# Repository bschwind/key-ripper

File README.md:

# key-ripper

A keyboard personalized for myself, designed in KiCad, with custom firmware written in Rust.

The story behind this board can be found in [this reddit post](https://www.reddit.com/r/MechanicalKeyboards/comments/vtlujd/i_built_a_keyboard_pcb_and_wrote_firmware_for_it/).

I also gave a (time-constrained) talk on making this keyboard which you can view [here](https://www.youtube.com/watch?v=x7LQevYn7d0).
Sadly I didn't get to cover everything I wanted to talk about when it comes to embedded Rust, but I hope you find it entertaining.

## Main Features and Requirements

* Be cheap to manufacture (can easily be ordered and fabricated by JLCPCB, uses an RP2040)
* USB C Connector
* Have dedicated function keys
* Reduce friction changing between a macbook keyboard and this one
* Stay relatively compact
* Full sized arrow keys with a gap (on the left and right) for easily finding the up arrow without looking
* No right shift key (this allows for the arrow keys to sit below the Enter key, and I never use right shift)
* Support for screw-in stabilizers first and foremost, along with snap-in stabilizers, and plate-mounted stabilizers when using a top plate
* Can sit on top of a macbook keyboard
* Easy to assemble - order a PCB, press it into the 3D printed case, and use 4 optional screws if the fit isn't snug
* Firmware written in Rust, debuggable with knurling-rs

## Setup

* Order a PCB with the production files from the [latest release](https://github.com/bschwind/key-ripper/releases).
* When you receive the board, plug it in via USB C and follow [the instruction to flash the firmware](https://github.com/bschwind/key-ripper/blob/main/firmware/README.md).

## 3D Printed Case

The STEP files for the case are available in the [case directory](./case).

They were produced with Rust bindings to OpenCascade. You can find the code for the keyboard case [here](https://github.com/bschwind/opencascade-rs/blob/2eefc2c0322c1cb65bd3279fbedeba416aef8858/examples/src/keyboard_case.rs).

The case can be printed as two separate parts with a dovetail connection (use your slicer and cut up the parts for whatever suits your print bed size), or it can be printed as one full piece.

The PCB can then be slotted into the case with the top edge first (the edge with the USB connector), then press the bottom edge in to fit it into the case. It's usually a snug fit. You can then use 4 M2x4 flat head "laptop screws" to secure the PCB in the middle two holes on the top and bottom edges.

The case feet can be printed and pressed directly into the bottom of the case. The STEP files were printed on a Prusa MK4 and MK3S, both of which had successful tolerances for the press-fit of the case feet.

## Current Version (v0.3.1)

[v0.3.1 PCBWay Production Files](https://github.com/bschwind/key-ripper/releases/tag/v0.3.1)

Version v0.3.1 adds an ESD protector on the USB connector, and was kindly sponsored and manufactured by PCBWay.

## v0.3

[v0.3 JLCPCB Production Files](https://github.com/bschwind/key-ripper/releases/tag/v0.3)

Version 0.3 adds some iterative hardware improvements over v0.2:

* Added support for threaded inserts on the PCB
* Added pass-through holes for M2 hex spacers
* Better impedance matching on the USB lines
* Added a cross-hatch copper pour to reduce warping compared to a solid copper pour
* Added some test points on the board
* Moved many components to a 1608 metric size for easier soldering
* Added an optional TRRS connector footprint for connecting to a debug probe
* Switched to a much smaller QSPI flash chip
* Added fancier patterns on the top and bottom plates

## v0.2

[v0.2 JLCPCB Production Files](https://github.com/bschwind/key-ripper/releases/tag/v0.2)

Version 0.2 improves upon some of the issues in v0.1, with some intentional choices that could be seen as a downgrade:

* Added a copper pour on both sides for a flatter PCB
* Shifted a few components away from the screw-in stabilizer holes to avoid screw washers touching the components
* Fixed some silkscreens for the reset and USB boot buttons
* Fixed the alignment of the F5 key
* **Controversial** - Changed the switch footprint to normal MX soldered switches instead of Kailh hotswap footprints. This allows for simpler boards that don't require a top plate.

## Version v0.1

Version 0.1 _works_ but there are some issues:

* The PCB warps during SMT reflow because there is a copper pour on only one side
* The silkscreens are not labeled well (SW1, SW2, SW3, etc. instead of Q, W, E, R, etc.)
* The F5 key is slightly more to the left of the F6 key than it should be, which leads to incompatible top plates between v0.1 and v0.2

Version 0.1 uses Kailh hotswap sockets. Combined with the top plate, this is good for trying out different switches, but adds complexity
in the build process. It requires more parts, and I had to 3D print 3.4mm M2 spacers.

[v0.1 JLCPCB Production Files](https://github.com/bschwind/key-ripper/releases/tag/v0.1)

## Production Files

For every PCB fabrication order, I make a github release and upload the files I used to make the order.

You can see a list of releases [here](https://github.com/bschwind/key-ripper/releases).

## Create a Gerber File

For most PCB fabrication shops, they expect gerber files, which are essentially files that describe the layout of pads/traces/geometry for each layer in a PCB. They also contain the drill locations if your PCB has any holes. All these layers should be placed in a directory and compressed to a zip file for uploading.

To create a gerber zip in KiCAD:

* Open up PCBNEW (KiCAD's PCB design tool)
* Select `File` -> `Plot`
* Select the following layers:
    * F.Cu
    * B.Cu
    * F.Paste
    * B.Paste
    * F.SilkS
    * B.SilkS
    * F.Mask
    * B.Mask
    * Edge.Cuts
* Leave all the other settings to their defaults
* Output to a directory named `gerber` (this is just convention, any name will do)
* Click `Plot`
* Next click `Generate Drill Files` with an `Excellon` drill file format, and a `Gerber` map file format
* Make sure the `Drill Units` are in `Millimeters`
* Output to the same directory you did for the previous gerber layers
* Click `Generate Drill File`
* Zip the `gerber` directory into a `gerber.zip` file and it's ready to upload!

**Note**: Check the PCB vendor's website for special KiCAD instructions, as they sometimes prefer certain settings when exporting.

OSHPark can directly accept `*.kicad_pcb` files so you don't need to export gerbers when ordering there.

## Create a Bill of Materials (for JLCPCB)

From the schematic viewer:

* Click the "BOM" button in the upper right toolbar
* Use the `bom_csv_grouped_by_value_with_fp`
* The output file won't have a `.csv` extension, so add it

Modify the CSV file:
* Rename the following columns:
    * `Ref` -> `Designator`
    * `Qnty` -> `Quantity`
* Delete the following columns:
    * `Cmp name`
    * `Description`
    * `Vendor`
* Add the following column:
    * `LCSC Part #`
* Remove any part rows you don't need to populate
* For each part, look it up on `jlcpcb.com/parts` and copy over both the footprint and the LCSC part number into their respective columns

In general, try to use as many "basic parts" as you can from JLCPCB. Each "extended part" costs an extra 300 yen per board.

## Create the Position File (for JCLPCB's pick-and-place machines)

From KiCad's PCB design tool:

* `File` -> `Fabrication Outputs` -> `Footprint Position (.pos) File`
* `Format`: `CSV`
* `Units`: `Millimeters`
* `Files`: `Single file for board`
* `Include footprints with SMD pads even if not marked Surface Mount`: `checked`
* Click `Generate Position File`

Modify the CSV file:

* Rename the following columns:
    * `Ref` -> `Designator`
    * `Qnty` -> `Quantity`
    * `Val` -> `Value`
    * `PosX` -> `Mid X`
    * `PosY` -> `Mid Y`
    * `Rot` -> `Rotation`
    * `Side` -> `Layer`

When uploading to JLCPCB, you may need to modify the rotation values. It will show you red dots on pin 1 for the relevant components, as well as a red `+` for components with polarity, so double check against your silkscreen and placement. Positive rotation goes counter-clockwise, so if you need to rotate a part counter-clockwise one turn, add 90 degrees. Subtract 90 to rotate one turn clockwise, and modulo 360 degrees to keep the overall rotation value positive.

## Firmware Debugging

Set the `DEFMT_LOG` environment variable.

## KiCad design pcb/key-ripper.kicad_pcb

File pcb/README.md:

# Notes

* The RP2040 samples the QSPI_SS line on boot. If this line is low, it will boot into its USB bootloader mode (i.e. enumerate as a mass storage device so you can upload new firmware). If this line is high on boot, it will start reading program instructions from the quad-SPI flash chip.

## Layout Notes

Just some measurements I've written down for my own designs are:
standard MX cutout - 14×14mm
distance between switches (center to center) - 19.05mm (both vertically and horizontally)
distance between caps - 0.95mm
distance between cap and case side - 0.475mm

Calculation example (60% case):
width of a case: 6 + (19.05 * 15) + (0.475 * 2) = 3mm bezel on each side, gap between case side and caps on each side, 15 keys in row.

Edit: 19.05mm distance between switches are only correct if they are two 1u keys. So for something like a 1.5u and 1u key distance between their centers would be (19.05 * 1.5)mm.

## TRRS Debug Connector

The footprint for the debug connector is a 3.5mm TRRS jack (part number PJ-320A, LCSC part number C2884926).

This footprint should be equivalent to the MJ-4PP-9 connector which is more easily found in Japan.

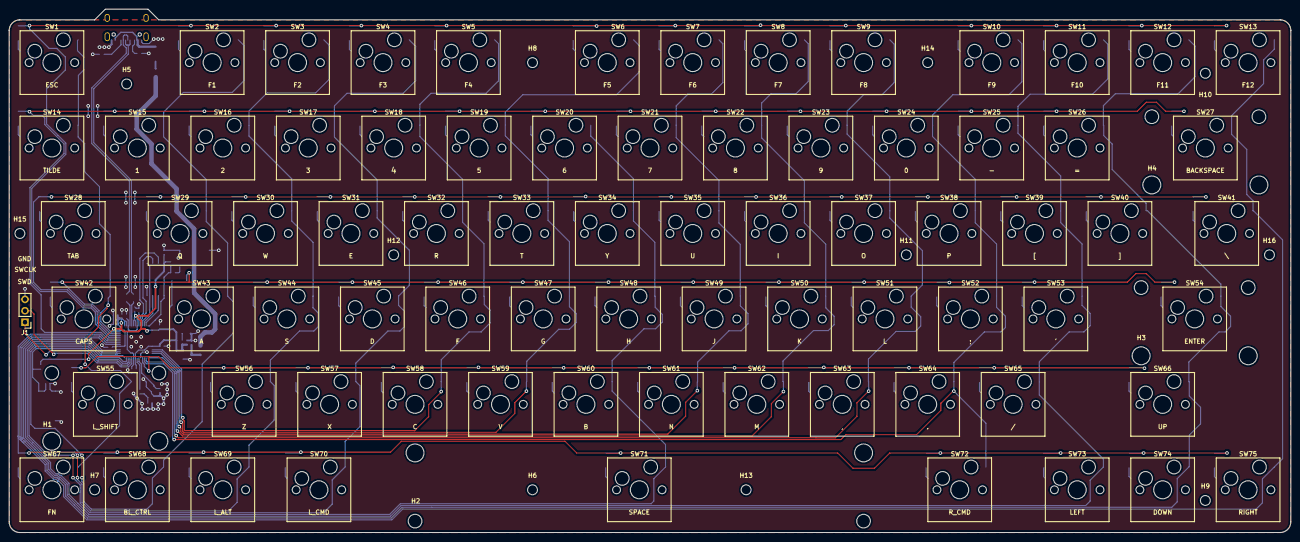
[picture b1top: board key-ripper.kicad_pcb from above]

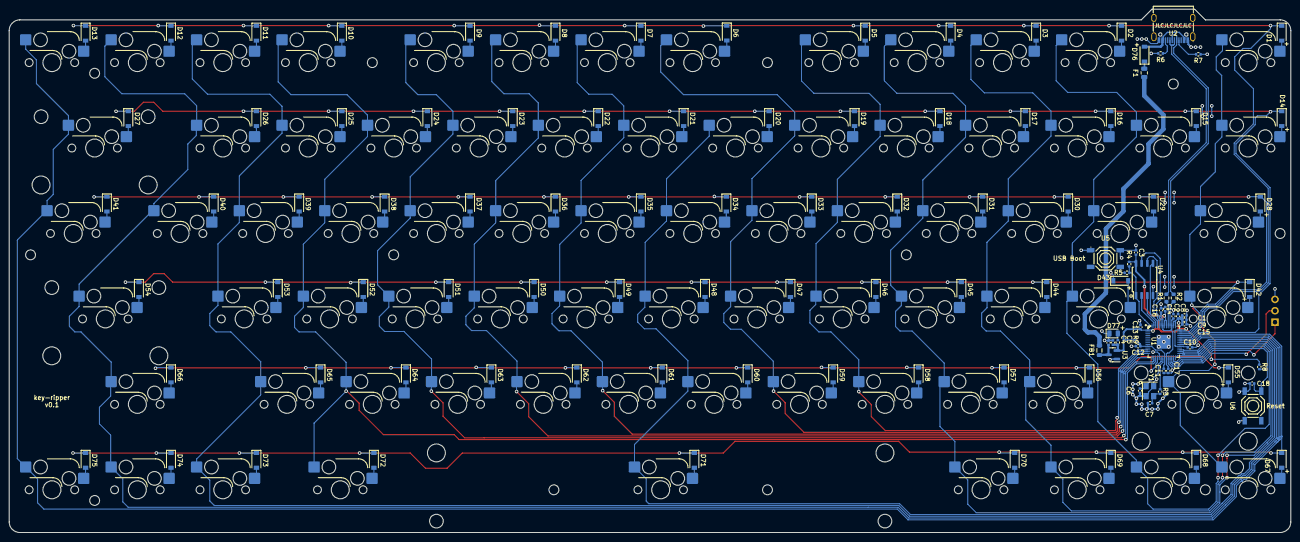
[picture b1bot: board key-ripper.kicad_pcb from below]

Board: 2 copper layers, 285.8 x 116.7 mm, 205 parts (113 on the bottom side), 122 nets.

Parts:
C1, C2, C4, C5: 1uF; C_0402_1005Metric
C3, C18: 0.1 uF; C_0402_1005Metric
C6, C7: 30pF; C_0402_1005Metric
C8, C9, C10, C11, C12, C13, C14, C15, C16, C17: 100nF; C_0402_1005Metric
D1, D2, D3, D4, D5, D6, D7, D8, D9, D10, D11, D12, D13, D14, D15, D16, D17, D18, D19, D20, D21, D22, D23, D24, D25, D26, D27, D28, D29, D30, D31, D32, D33, D34, D35, D36, D37, D38, D39, D40, D41, D42, D43, D44, D45, D46, D47, D48, D49, D50, D51, D52, D53, D54, D55, D56, D57, D58, D59, D60, D61, D62, D63, D64, D65, D66, D67, D68, D69, D70, D71, D72, D73, D74, D75: D_Small; D_SOD-123
D76: Schottky 5819W; D_SOD-123
D77: Power LED (Green); LED_0805_2012Metric
F1: TLC_PSMD050; Fuse_0805_2012Metric
FB1: 100@100MHz; L_0805_2012Metric
H1: L_SHIFT_STABILIZER; Stabilizer_Cherry_MX_2.00u
H2: SPACE_STABILIZER; Stabilizer_Cherry_MX_6.25u
H3: ENTER_STABILIZER; Stabilizer_Cherry_MX_2.00u
H4: BACKSPACE_STABILIZER; Stabilizer_Cherry_MX_2.00u
H5, H6, H7, H8, H9, H10, H11, H12, H13, H14, H15, H16: M_HOLE; MountingHole_2.2mm_M2
J1: Conn_01x03; PinHeader_1x03_P2.54mm_Vertical
R1, R2: 27 ohm; R_0603_1608Metric
R3, R5: 1k ohm; R_0402_1005Metric
R4, R8: 10k ohm; R_0402_1005Metric
R6, R7: 5.1k; R_0402_1005Metric
R9: 1k5 ohm; R_0402_1005Metric
SW1: ESC; SW_Hotswap_Kailh_MX_1.00u
SW2: F1; SW_Hotswap_Kailh_MX_1.00u
SW3: F2; SW_Hotswap_Kailh_MX_1.00u
SW4: F3; SW_Hotswap_Kailh_MX_1.00u
SW5: F4; SW_Hotswap_Kailh_MX_1.00u
SW6: F5; SW_Hotswap_Kailh_MX_1.00u
SW7: F6; SW_Hotswap_Kailh_MX_1.00u
SW8: F7; SW_Hotswap_Kailh_MX_1.00u
SW9: F8; SW_Hotswap_Kailh_MX_1.00u
SW10: F9; SW_Hotswap_Kailh_MX_1.00u
SW11: F10; SW_Hotswap_Kailh_MX_1.00u
SW12: F11; SW_Hotswap_Kailh_MX_1.00u
SW13: F12; SW_Hotswap_Kailh_MX_1.00u
SW14: TILDE; SW_Hotswap_Kailh_MX_1.00u
SW15: 1; SW_Hotswap_Kailh_MX_1.00u
SW16: 2; SW_Hotswap_Kailh_MX_1.00u
SW17: 3; SW_Hotswap_Kailh_MX_1.00u
SW18: 4; SW_Hotswap_Kailh_MX_1.00u
SW19: 5; SW_Hotswap_Kailh_MX_1.00u
SW20: 6; SW_Hotswap_Kailh_MX_1.00u
SW21: 7; SW_Hotswap_Kailh_MX_1.00u
SW22: 8; SW_Hotswap_Kailh_MX_1.00u
SW23: 9; SW_Hotswap_Kailh_MX_1.00u
SW24: 0; SW_Hotswap_Kailh_MX_1.00u
SW25: -; SW_Hotswap_Kailh_MX_1.00u
SW26: =; SW_Hotswap_Kailh_MX_1.00u
SW27: BACKSPACE; SW_Hotswap_Kailh_MX_2.00u
SW28: TAB; SW_Hotswap_Kailh_MX_1.50u
SW29: Q; SW_Hotswap_Kailh_MX_1.00u
SW30: W; SW_Hotswap_Kailh_MX_1.00u
SW31: E; SW_Hotswap_Kailh_MX_1.00u
SW32: R; SW_Hotswap_Kailh_MX_1.00u
SW33: T; SW_Hotswap_Kailh_MX_1.00u
SW34: Y; SW_Hotswap_Kailh_MX_1.00u
SW35: U; SW_Hotswap_Kailh_MX_1.00u
SW36: I; SW_Hotswap_Kailh_MX_1.00u
SW37: O; SW_Hotswap_Kailh_MX_1.00u
SW38: P; SW_Hotswap_Kailh_MX_1.00u
SW39: [; SW_Hotswap_Kailh_MX_1.00u
SW40: ]; SW_Hotswap_Kailh_MX_1.00u
SW41: \; SW_Hotswap_Kailh_MX_1.50u
SW42: CAPS; SW_Hotswap_Kailh_MX_1.75u
SW43: A; SW_Hotswap_Kailh_MX_1.00u
SW44: S; SW_Hotswap_Kailh_MX_1.00u
SW45: D; SW_Hotswap_Kailh_MX_1.00u
SW46: F; SW_Hotswap_Kailh_MX_1.00u
SW47: G; SW_Hotswap_Kailh_MX_1.00u
SW48: H; SW_Hotswap_Kailh_MX_1.00u
SW49: J; SW_Hotswap_Kailh_MX_1.00u
SW50: K; SW_Hotswap_Kailh_MX_1.00u
SW51: L; SW_Hotswap_Kailh_MX_1.00u
SW52: ;; SW_Hotswap_Kailh_MX_1.00u
SW53: '; SW_Hotswap_Kailh_MX_1.00u
SW54: ENTER; SW_Hotswap_Kailh_MX_2.25u
SW55: L_SHIFT; SW_Hotswap_Kailh_MX_2.25u
SW56: Z; SW_Hotswap_Kailh_MX_1.00u
SW57: X; SW_Hotswap_Kailh_MX_1.00u
SW58: C; SW_Hotswap_Kailh_MX_1.00u
SW59: V; SW_Hotswap_Kailh_MX_1.00u
SW60: B; SW_Hotswap_Kailh_MX_1.00u
SW61: N; SW_Hotswap_Kailh_MX_1.00u
SW62: M; SW_Hotswap_Kailh_MX_1.00u
SW63: ,; SW_Hotswap_Kailh_MX_1.00u
SW64: .; SW_Hotswap_Kailh_MX_1.00u
SW65: /; SW_Hotswap_Kailh_MX_1.00u
SW66: UP; SW_Hotswap_Kailh_MX_1.00u
SW67: FN; SW_Hotswap_Kailh_MX_1.00u
SW68: BL_CTRL; SW_Hotswap_Kailh_MX_1.00u
SW69: L_ALT; SW_Hotswap_Kailh_MX_1.00u
SW70: L_CMD; SW_Hotswap_Kailh_MX_1.25u
SW71: SPACE; SW_Hotswap_Kailh_MX_6.25u
SW72: R_CMD; SW_Hotswap_Kailh_MX_1.25u
SW73: LEFT; SW_Hotswap_Kailh_MX_1.00u
SW74: DOWN; SW_Hotswap_Kailh_MX_1.00u
SW75: RIGHT; SW_Hotswap_Kailh_MX_1.00u
U1: RP2040; rp2040
U2: TYPE-C-31-M-12; simple-usb-c
U3: XC6206PxxxMR; SOT-23
U4: W25Q128JVS; SOIC-8_5.23x5.23mm_P1.27mm
U5: USB Boot; tactile-switch
U6: Reset; tactile-switch
Y1: 12MHz - 20pF; Crystal_SMD_3225-4Pin_3.2x2.5mm

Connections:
+1V1: C2.1, C16.1, C17.1, U1.23 (DVDD), U1.45 (VREG_VOUT), U1.50 (DVDD)
+3V3: C1.1, C3.1, C5.1, C8.1, C9.1, C10.1, C11.1, C12.1, C13.1, C14.1, C15.1, R4.1, R8.2, R9.1, U1.1 (IOVDD), U1.10 (IOVDD), U1.22 (IOVDD), U1.33 (IOVDD), U1.42 (IOVDD), U1.43 (ADC_AVDD), U1.44 (VREG_IN), U1.48 (USB_VDD), U1.49 (IOVDD), U3.2 (VO), U4.8 (VCC)
+5V: C4.1, FB1.2, U3.3 (VI)
CC1: R7.1, U2.A5 (CC1)
CC2: R6.1, U2.B5 (CC2)
CLM0: SW1.2, SW14.2, SW28.2, SW42.2, SW55.2, SW67.2, U1.41 (GPIO29_ADC3)
CLM1: SW2.2, SW15.2, SW29.2, SW43.2, SW68.2, U1.27 (GPIO16)
CLM2: SW3.2, SW16.2, SW30.2, SW44.2, SW56.2, SW69.2, U1.28 (GPIO17)
CLM3: SW4.2, SW17.2, SW31.2, SW45.2, SW57.2, SW70.2, U1.29 (GPIO18)
CLM4: SW5.2, SW18.2, SW32.2, SW46.2, SW58.2, U1.12 (GPIO9)
CLM5: SW6.2, SW19.2, SW33.2, SW47.2, SW59.2, U1.13 (GPIO10)
CLM6: SW20.2, SW34.2, SW48.2, SW60.2, SW71.2, U1.30 (GPIO19)
CLM7: SW7.2, SW21.2, SW35.2, SW49.2, SW61.2, U1.14 (GPIO11)
CLM8: SW8.2, SW22.2, SW36.2, SW50.2, SW62.2, U1.15 (GPIO12)
CLM9: SW9.2, SW23.2, SW37.2, SW51.2, SW63.2, U1.16 (GPIO13)
CLM10: SW10.2, SW24.2, SW38.2, SW52.2, SW64.2, SW72.2, U1.17 (GPIO14)
CLM11: SW11.2, SW25.2, SW39.2, SW53.2, SW65.2, SW73.2, U1.31 (GPIO20)
CLM12: SW12.2, SW26.2, SW40.2, SW54.2, SW66.2, SW74.2, U1.34 (GPIO22)
CLM13: SW13.2, SW27.2, SW41.2, SW75.2, U1.35 (GPIO23)
GND: C1.2, C2.2, C3.2, C4.2, C5.2, C6.2, C7.2, C8.2, C9.2, C10.2, C11.2, C12.2, C13.2, C14.2, C15.2, C16.2, C17.2, C18.2, D77.1 (K), J1.3, R6.2, R7.2, U1.19 (TESTEN), U1.57 (GND), U2.A1 (GND), U2.A12 (GND), U2.B1 (GND), U2.B12 (GND), U3.1 (GND), U4.4 (GND), U5.1 (A), U5.2 (B), U6.1 (A), U6.2 (B), Y1.2, Y1.4
unnamed: D1.2 (A), SW1.1
unnamed: D2.2 (A), SW2.1
unnamed: D3.2 (A), SW3.1
unnamed: D4.2 (A), SW4.1
unnamed: D5.2 (A), SW5.1
unnamed: D6.2 (A), SW6.1
unnamed: D7.2 (A), SW7.1
unnamed: D8.2 (A), SW8.1
unnamed: D9.2 (A), SW9.1
unnamed: D10.2 (A), SW10.1
unnamed: D11.2 (A), SW11.1
unnamed: D12.2 (A), SW12.1
unnamed: D13.2 (A), SW13.1
unnamed: D14.2 (A), SW14.1
unnamed: D15.2 (A), SW15.1
unnamed: D16.2 (A), SW16.1
unnamed: D17.2 (A), SW17.1
unnamed: D18.2 (A), SW18.1
unnamed: D19.2 (A), SW19.1
unnamed: D20.2 (A), SW20.1
unnamed: D21.2 (A), SW21.1
unnamed: D22.2 (A), SW22.1
unnamed: D23.2 (A), SW23.1
unnamed: D24.2 (A), SW24.1
unnamed: D25.2 (A), SW25.1
unnamed: D26.2 (A), SW26.1
unnamed: D27.2 (A), SW27.1
unnamed: D28.2 (A), SW28.1
unnamed: D29.2 (A), SW29.1
unnamed: D30.2 (A), SW30.1
unnamed: D31.2 (A), SW31.1
unnamed: D32.2 (A), SW32.1
unnamed: D33.2 (A), SW33.1
unnamed: D34.2 (A), SW34.1
unnamed: D35.2 (A), SW35.1
unnamed: D36.2 (A), SW36.1
unnamed: D37.2 (A), SW37.1
unnamed: D38.2 (A), SW38.1
unnamed: D39.2 (A), SW39.1
unnamed: D40.2 (A), SW40.1
unnamed: D41.2 (A), SW41.1
unnamed: D42.2 (A), SW42.1
unnamed: D43.2 (A), SW43.1
unnamed: D44.2 (A), SW44.1
unnamed: D45.2 (A), SW45.1
unnamed: D46.2 (A), SW46.1
unnamed: D47.2 (A), SW47.1
unnamed: D48.2 (A), SW48.1
unnamed: D49.2 (A), SW49.1
unnamed: D50.2 (A), SW50.1
unnamed: D51.2 (A), SW51.1
unnamed: D52.2 (A), SW52.1
unnamed: D53.2 (A), SW53.1
unnamed: D54.2 (A), SW54.1
unnamed: D55.2 (A), SW55.1
unnamed: D56.2 (A), SW56.1
unnamed: D57.2 (A), SW57.1
unnamed: D58.2 (A), SW58.1
unnamed: D59.2 (A), SW59.1
unnamed: D60.2 (A), SW60.1
unnamed: D61.2 (A), SW61.1
unnamed: D62.2 (A), SW62.1
unnamed: D63.2 (A), SW63.1
unnamed: D64.2 (A), SW64.1
unnamed: D65.2 (A), SW65.1
unnamed: D66.2 (A), SW66.1
unnamed: D67.2 (A), SW67.1
unnamed: D68.2 (A), SW68.1
unnamed: D69.2 (A), SW69.1
unnamed: D70.2 (A), SW70.1
unnamed: D71.2 (A), SW71.1
unnamed: D72.2 (A), SW72.1
unnamed: D73.2 (A), SW73.1
unnamed: D74.2 (A), SW74.1
unnamed: D75.2 (A), SW75.1
unnamed: D76.1 (K), F1.1
unnamed: D77.2 (A), R9.2
unnamed: F1.2, FB1.1
unnamed: R5.2, U5.3 (C), U5.4 (D)
OSC_IN: C7.1, R3.1, Y1.3
OSC_OUT: C6.1, U1.20 (XIN), Y1.1
QSPI_SCLK: U1.52 (QSPI_SCLK), U4.6 (CLK)
QSPI_SD0: U1.53 (QSPI_SD0), U4.5 (DI(IO0))
QSPI_SD1: U1.55 (QSPI_SD1), U4.2 (DO(IO1))
QSPI_SD2: U1.54 (QSPI_SD2), U4.3 (IO2)
QSPI_SD3: U1.51 (QSPI_SD3), U4.7 (IO3)
QSPI_SS: R4.2, R5.1, U1.56 (QSPI_SS), U4.1 (~CS)
ROW0: D1.1 (K), D2.1 (K), D3.1 (K), D4.1 (K), D5.1 (K), D6.1 (K), D7.1 (K), D8.1 (K), D9.1 (K), D10.1 (K), D11.1 (K), D12.1 (K), D13.1 (K), U1.38 (GPIO26_ADC0)
ROW1: D14.1 (K), D15.1 (K), D16.1 (K), D17.1 (K), D18.1 (K), D19.1 (K), D20.1 (K), D21.1 (K), D22.1 (K), D23.1 (K), D24.1 (K), D25.1 (K), D26.1 (K), D27.1 (K), U1.37 (GPIO25)
ROW2: D28.1 (K), D29.1 (K), D30.1 (K), D31.1 (K), D32.1 (K), D33.1 (K), D34.1 (K), D35.1 (K), D36.1 (K), D37.1 (K), D38.1 (K), D39.1 (K), D40.1 (K), D41.1 (K), U1.39 (GPIO27_ADC1)
ROW3: D42.1 (K), D43.1 (K), D44.1 (K), D45.1 (K), D46.1 (K), D47.1 (K), D48.1 (K), D49.1 (K), D50.1 (K), D51.1 (K), D52.1 (K), D53.1 (K), D54.1 (K), U1.40 (GPIO28_ADC2)
ROW4: D55.1 (K), D56.1 (K), D57.1 (K), D58.1 (K), D59.1 (K), D60.1 (K), D61.1 (K), D62.1 (K), D63.1 (K), D64.1 (K), D65.1 (K), D66.1 (K), U1.18 (GPIO15)
ROW5: D67.1 (K), D68.1 (K), D69.1 (K), D70.1 (K), D71.1 (K), D72.1 (K), D73.1 (K), D74.1 (K), D75.1 (K), U1.36 (GPIO24)
RUN: C18.1, R8.1, U1.26 (RUN), U6.3 (C), U6.4 (D)
SWCLK: J1.2, U1.24 (SWCLK)
SWD: J1.1, U1.25 (SWD)
USB+: R1.2, U2.A6 (DP1), U2.B6 (DP2)
USB-: R2.2, U2.A7 (DN1), U2.B7 (DN2)
USB_MCU+: R1.1, U1.47 (USB_DP)
USB_MCU-: R2.1, U1.46 (USB_DM)
VBUS: D76.2 (A), U2.A4 (VBUS), U2.A9 (VBUS), U2.B4 (VBUS), U2.B9 (VBUS)
XOUT_MCU: R3.2, U1.21 (XOUT)

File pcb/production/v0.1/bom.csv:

Designator,Quantity,Value,Footprint,LCSC Part #
"C1, C2, C4, C5,",4,1uF,Capacitor_SMD:C_0402_1005Metric,C52923
"C3, C18,",2,0.1 uF,Capacitor_SMD:C_0402_1005Metric,C307331
"C6, C7,",2,30pF,Capacitor_SMD:C_0402_1005Metric,C1570
"C8, C9, C10, C11, C12, C13, C14, C15, C16, C17,",10,100nF,Capacitor_SMD:C_0402_1005Metric,C307331
"D1, D2, D3, D4, D5, D6, D7, D8, D9, D10, D11, D12, D13, D14, D15, D16, D17, D18, D19, D20, D21, D22, D23, D24, D25, D26, D27, D28, D29, D30, D31, D32, D33, D34, D35, D36, D37, D38, D39, D40, D41, D42, D43, D44, D45, D46, D47, D48, D49, D50, D51, D52, D53, D54, D55, D56, D57, D58, D59, D60, D61, D62, D63, D64, D65, D66, D67, D68, D69, D70, D71, D72, D73, D74, D75,",75,D_Small,Diode_SMD:D_SOD-123,C81598
"D76,",1,Schottky 5819W,Diode_SMD:D_SOD-123,C8598
"D77,",1,Power LED (Green),LED_SMD:LED_0805_2012Metric,C2297
"F1,",1,TLC_PSMD050,Fuse:Fuse_0805_2012Metric,C261942
"FB1,",1,100@100MHz,Inductor_SMD:L_0805_2012Metric,C1015
"R1, R2,",2,27 ohm,Resistor_SMD:R_0603_1608Metric,C25190
"R3, R5,",2,1k ohm,Resistor_SMD:R_0402_1005Metric,C11702
"R4, R8,",2,10k ohm,Resistor_SMD:R_0402_1005Metric,C25744
"R6, R7,",2,5.1k,Resistor_SMD:R_0402_1005Metric,C25905
"R9,",1,1k5 ohm,Resistor_SMD:R_0402_1005Metric,C25867
"SW1,",1,ESC,Switch_Keyboard_Hotswap_Kailh:SW_Hotswap_Kailh_MX_1.00u,C2803348
"SW2,",1,F1,Switch_Keyboard_Hotswap_Kailh:SW_Hotswap_Kailh_MX_1.00u,C2803348
"SW3,",1,F2,Switch_Keyboard_Hotswap_Kailh:SW_Hotswap_Kailh_MX_1.00u,C2803348
"SW4,",1,F3,Switch_Keyboard_Hotswap_Kailh:SW_Hotswap_Kailh_MX_1.00u,C2803348
"SW5,",1,F4,Switch_Keyboard_Hotswap_Kailh:SW_Hotswap_Kailh_MX_1.00u,C2803348
"SW6,",1,F5,Switch_Keyboard_Hotswap_Kailh:SW_Hotswap_Kailh_MX_1.00u,C2803348
"SW7,",1,F6,Switch_Keyboard_Hotswap_Kailh:SW_Hotswap_Kailh_MX_1.00u,C2803348
"SW8,",1,F7,Switch_Keyboard_Hotswap_Kailh:SW_Hotswap_Kailh_MX_1.00u,C2803348
"SW9,",1,F8,Switch_Keyboard_Hotswap_Kailh:SW_Hotswap_Kailh_MX_1.00u,C2803348
"SW10,",1,F9,Switch_Keyboard_Hotswap_Kailh:SW_Hotswap_Kailh_MX_1.00u,C2803348
"SW11,",1,F10,Switch_Keyboard_Hotswap_Kailh:SW_Hotswap_Kailh_MX_1.00u,C2803348
"SW12,",1,F11,Switch_Keyboard_Hotswap_Kailh:SW_Hotswap_Kailh_MX_1.00u,C2803348
"SW13,",1,F12,Switch_Keyboard_Hotswap_Kailh:SW_Hotswap_Kailh_MX_1.00u,C2803348
"SW14,",1,TILDE,Switch_Keyboard_Hotswap_Kailh:SW_Hotswap_Kailh_MX_1.00u,C2803348
"SW15,",1,1,Switch_Keyboard_Hotswap_Kailh:SW_Hotswap_Kailh_MX_1.00u,C2803348
"SW16,",1,2,Switch_Keyboard_Hotswap_Kailh:SW_Hotswap_Kailh_MX_1.00u,C2803348
"SW17,",1,3,Switch_Keyboard_Hotswap_Kailh:SW_Hotswap_Kailh_MX_1.00u,C2803348
"SW18,",1,4,Switch_Keyboard_Hotswap_Kailh:SW_Hotswap_Kailh_MX_1.00u,C2803348
"SW19,",1,5,Switch_Keyboard_Hotswap_Kailh:SW_Hotswap_Kailh_MX_1.00u,C2803348
"SW20,",1,6,Switch_Keyboard_Hotswap_Kailh:SW_Hotswap_Kailh_MX_1.00u,C2803348
"SW21,",1,7,Switch_Keyboard_Hotswap_Kailh:SW_Hotswap_Kailh_MX_1.00u,C2803348
"SW22,",1,8,Switch_Keyboard_Hotswap_Kailh:SW_Hotswap_Kailh_MX_1.00u,C2803348
"SW23,",1,9,Switch_Keyboard_Hotswap_Kailh:SW_Hotswap_Kailh_MX_1.00u,C2803348
"SW24,",1,0,Switch_Keyboard_Hotswap_Kailh:SW_Hotswap_Kailh_MX_1.00u,C2803348
"SW25,",1,-,Switch_Keyboard_Hotswap_Kailh:SW_Hotswap_Kailh_MX_1.00u,C2803348
"SW26,",1,=,Switch_Keyboard_Hotswap_Kailh:SW_Hotswap_Kailh_MX_1.00u,C2803348
"SW27,",1,BACKSPACE,Switch_Keyboard_Hotswap_Kailh:SW_Hotswap_Kailh_MX_2.00u,C2803348
"SW28,",1,TAB,Switch_Keyboard_Hotswap_Kailh:SW_Hotswap_Kailh_MX_1.50u,C2803348
"SW29,",1,Q,Switch_Keyboard_Hotswap_Kailh:SW_Hotswap_Kailh_MX_1.00u,C2803348
"SW30,",1,W,Switch_Keyboard_Hotswap_Kailh:SW_Hotswap_Kailh_MX_1.00u,C2803348
"SW31,",1,E,Switch_Keyboard_Hotswap_Kailh:SW_Hotswap_Kailh_MX_1.00u,C2803348
"SW32,",1,R,Switch_Keyboard_Hotswap_Kailh:SW_Hotswap_Kailh_MX_1.00u,C2803348
"SW33,",1,T,Switch_Keyboard_Hotswap_Kailh:SW_Hotswap_Kailh_MX_1.00u,C2803348
"SW34,",1,Y,Switch_Keyboard_Hotswap_Kailh:SW_Hotswap_Kailh_MX_1.00u,C2803348
"SW35,",1,U,Switch_Keyboard_Hotswap_Kailh:SW_Hotswap_Kailh_MX_1.00u,C2803348
"SW36,",1,I,Switch_Keyboard_Hotswap_Kailh:SW_Hotswap_Kailh_MX_1.00u,C2803348
"SW37,",1,O,Switch_Keyboard_Hotswap_Kailh:SW_Hotswap_Kailh_MX_1.00u,C2803348
"SW38,",1,P,Switch_Keyboard_Hotswap_Kailh:SW_Hotswap_Kailh_MX_1.00u,C2803348
"SW39,",1,[,Switch_Keyboard_Hotswap_Kailh:SW_Hotswap_Kailh_MX_1.00u,C2803348
"SW40,",1,],Switch_Keyboard_Hotswap_Kailh:SW_Hotswap_Kailh_MX_1.00u,C2803348
"SW41,",1,\,Switch_Keyboard_Hotswap_Kailh:SW_Hotswap_Kailh_MX_1.50u,C2803348
"SW42,",1,CAPS,Switch_Keyboard_Hotswap_Kailh:SW_Hotswap_Kailh_MX_1.75u,C2803348
"SW43,",1,A,Switch_Keyboard_Hotswap_Kailh:SW_Hotswap_Kailh_MX_1.00u,C2803348
"SW44,",1,S,Switch_Keyboard_Hotswap_Kailh:SW_Hotswap_Kailh_MX_1.00u,C2803348
"SW45,",1,D,Switch_Keyboard_Hotswap_Kailh:SW_Hotswap_Kailh_MX_1.00u,C2803348
"SW46,",1,F,Switch_Keyboard_Hotswap_Kailh:SW_Hotswap_Kailh_MX_1.00u,C2803348
"SW47,",1,G,Switch_Keyboard_Hotswap_Kailh:SW_Hotswap_Kailh_MX_1.00u,C2803348
"SW48,",1,H,Switch_Keyboard_Hotswap_Kailh:SW_Hotswap_Kailh_MX_1.00u,C2803348
"SW49,",1,J,Switch_Keyboard_Hotswap_Kailh:SW_Hotswap_Kailh_MX_1.00u,C2803348
"SW50,",1,K,Switch_Keyboard_Hotswap_Kailh:SW_Hotswap_Kailh_MX_1.00u,C2803348
"SW51,",1,L,Switch_Keyboard_Hotswap_Kailh:SW_Hotswap_Kailh_MX_1.00u,C2803348
"SW52,",1,;,Switch_Keyboard_Hotswap_Kailh:SW_Hotswap_Kailh_MX_1.00u,C2803348
"SW53,",1,',Switch_Keyboard_Hotswap_Kailh:SW_Hotswap_Kailh_MX_1.00u,C2803348
"SW54,",1,ENTER,Switch_Keyboard_Hotswap_Kailh:SW_Hotswap_Kailh_MX_2.25u,C2803348
"SW55,",1,L_SHIFT,Switch_Keyboard_Hotswap_Kailh:SW_Hotswap_Kailh_MX_2.25u,C2803348
"SW56,",1,Z,Switch_Keyboard_Hotswap_Kailh:SW_Hotswap_Kailh_MX_1.00u,C2803348
"SW57,",1,X,Switch_Keyboard_Hotswap_Kailh:SW_Hotswap_Kailh_MX_1.00u,C2803348
"SW58,",1,C,Switch_Keyboard_Hotswap_Kailh:SW_Hotswap_Kailh_MX_1.00u,C2803348
"SW59,",1,V,Switch_Keyboard_Hotswap_Kailh:SW_Hotswap_Kailh_MX_1.00u,C2803348
"SW60,",1,B,Switch_Keyboard_Hotswap_Kailh:SW_Hotswap_Kailh_MX_1.00u,C2803348
"SW61,",1,N,Switch_Keyboard_Hotswap_Kailh:SW_Hotswap_Kailh_MX_1.00u,C2803348
"SW62,",1,M,Switch_Keyboard_Hotswap_Kailh:SW_Hotswap_Kailh_MX_1.00u,C2803348
"SW63,",1,",",Switch_Keyboard_Hotswap_Kailh:SW_Hotswap_Kailh_MX_1.00u,C2803348
"SW64,",1,.,Switch_Keyboard_Hotswap_Kailh:SW_Hotswap_Kailh_MX_1.00u,C2803348
"SW65,",1,/,Switch_Keyboard_Hotswap_Kailh:SW_Hotswap_Kailh_MX_1.00u,C2803348
"SW66,",1,UP,Switch_Keyboard_Hotswap_Kailh:SW_Hotswap_Kailh_MX_1.00u,C2803348
"SW67,",1,FN,Switch_Keyboard_Hotswap_Kailh:SW_Hotswap_Kailh_MX_1.00u,C2803348
"SW68,",1,BL_CTRL,Switch_Keyboard_Hotswap_Kailh:SW_Hotswap_Kailh_MX_1.00u,C2803348
"SW69,",1,L_ALT,Switch_Keyboard_Hotswap_Kailh:SW_Hotswap_Kailh_MX_1.00u,C2803348
"SW70,",1,L_CMD,Switch_Keyboard_Hotswap_Kailh:SW_Hotswap_Kailh_MX_1.25u,C2803348
"SW71,",1,SPACE,Switch_Keyboard_Hotswap_Kailh:SW_Hotswap_Kailh_MX_6.25u,C2803348
"SW72,",1,R_CMD,Switch_Keyboard_Hotswap_Kailh:SW_Hotswap_Kailh_MX_1.25u,C2803348
"SW73,",1,LEFT,Switch_Keyboard_Hotswap_Kailh:SW_Hotswap_Kailh_MX_1.00u,C2803348
"SW74,",1,DOWN,Switch_Keyboard_Hotswap_Kailh:SW_Hotswap_Kailh_MX_1.00u,C2803348
"SW75,",1,RIGHT,Switch_Keyboard_Hotswap_Kailh:SW_Hotswap_Kailh_MX_1.00u,C2803348
"U1,",1,RP2040,footprints:rp2040,C2040
"U2,",1,TYPE-C-31-M-12,footprints:simple-usb-c,C165948
"U3,",1,XC6206PxxxMR,Package_TO_SOT_SMD:SOT-23,C5446
"U4,",1,W25Q128JVS,Package_SO:SOIC-8_5.23x5.23mm_P1.27mm,C97521
"U5,",1,USB Boot,footprints:tactile-switch,C318884
"U6,",1,Reset,footprints:tactile-switch,C318884
"Y1,",1,12MHz - 20pF,Crystal:Crystal_SMD_3225-4Pin_3.2x2.5mm,C9002

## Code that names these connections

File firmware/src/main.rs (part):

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    // Set up keyboard matrix pins.
    let mut rows: [&mut dyn InputPin<Error = Infallible>; NUM_ROWS] = [
        &mut pins.gpio26.into_pull_down_input(),
        &mut pins.gpio25.into_pull_down_input(),
        &mut pins.gpio27.into_pull_down_input(),
        &mut pins.gpio28.into_pull_down_input(),
        &mut pins.gpio15.into_pull_down_input(),
        &mut pins.gpio24.into_pull_down_input(),
    ];

    let mut cols: [&mut dyn OutputPin<Error = Infallible>; NUM_COLS] = [
        &mut pins.gpio29.into_push_pull_output(),
        &mut pins.gpio16.into_push_pull_output(),
        &mut pins.gpio17.into_push_pull_output(),
        &mut pins.gpio18.into_push_pull_output(),
        &mut pins.gpio9.into_push_pull_output(),
        &mut pins.gpio10.into_push_pull_output(),
        &mut pins.gpio19.into_push_pull_output(),
        &mut pins.gpio11.into_push_pull_output(),
        &mut pins.gpio12.into_push_pull_output(),
        &mut pins.gpio13.into_push_pull_output(),
        &mut pins.gpio14.into_push_pull_output(),
        &mut pins.gpio20.into_push_pull_output(),
        &mut pins.gpio22.into_push_pull_output(),
        &mut pins.gpio23.into_push_pull_output(),
    ];

    // Initialize a delay for accurate sleeping.
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
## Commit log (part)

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2022-06-19 Make the edge cutouts even smaller
2022-06-19 Small adjustments
2022-06-20 Add some layout notes
2022-06-21 Tune the skew of the USB differential pair
2022-06-21 Undo skew tuning, probably not needed for now
2022-06-21 Everything is ready to be routed
2022-06-21 More power routing
2022-06-21 Move row vias up a bit
2022-06-22 Move the diodes to a better spot
2022-06-22 Clean up stray wires
2022-06-22 Connect the columns together
2022-06-22 Connect the rows together
2022-06-22 Starting more simplifications
2022-06-22 Route rows more consistently
2022-06-22 Resize the column connectors
2022-06-22 Connect 3v3 power rails again
2022-06-22 Actual progress on matrix routing
2022-06-22 Finally connect the whole matrix
2022-06-24 More matrix wiring cleanup
2022-06-24 Connect 1v1 lines
2022-06-24 Place the rest of the components
2022-06-25 Connect switch rows together, clean up stray traces
2022-06-26 Connect more components and nets
2022-06-26 More connections
2022-06-26 Track adjustments
2022-06-26 Tidy up some traces that violated DRC
2022-06-26 More DRC checks
2022-06-27 Move key names to silk screen
2022-06-27 Reposition key name silk screens
2022-06-27 Add JCL order number silkscreen
2022-06-27 Add button labels
2022-06-27 Add pin 1 markers and diode polarity markers
2022-06-28 Fix the SWD silkscreen
2022-06-28 Update parts list, add start of BOM list
2022-06-28 Add v0.1 silkscreen
2022-06-28 Update parts list
2022-06-28 Double check footprints and part numbers
2022-06-28 Use JLC footprint names for all parts
2022-06-28 Export gerber files
2022-06-29 Move entire file down to be in positive coordinates
2022-06-29 New gerber files
2022-06-29 Update PCB with new matrix layout
2022-06-29 More groupings and layout
2022-06-29 Reattach USB C differential pair
2022-06-29 Add key stabilizers
2022-06-29 Rearrange keys in the matrix for better routing
2022-06-29 Organize key matrix vias
2022-07-06 Add firmware skeleton code
2022-07-06 Basic version of the firmware is working!
2022-07-06 Fix row and column sizes
2022-07-06 Add keycodes and matrix
2022-07-06 Use the mapping matrix to build a report
2022-07-07 Fix matrix mapping formatting, add missing keyboard row
2022-07-07 Add license files
2022-07-07 Remove debug comment
2022-07-07 Move licenses to the top level directory
2022-07-09 Add support for probe-run tooling
2022-07-09 Add support for probe-run tooling (#9)
2022-07-09 Add a working keyboard HID descriptor
2022-07-09 Make the formatting more compact
2022-07-09 Working HID Descriptor (#10)
    * Add a working keyboard HID descriptor
    * Fix a comment, code formatting
    * Make the formatting more compact
2022-07-10 Don't slow the key scan rate just because we would have blocked
2022-07-10 Fix the placement of the F5 key
2022-07-10 Add a ground pour and stitching vias
2022-07-10 Move some components a little farther away from the screw-in stabilizers
2022-07-10 Use the soldered MX footprint instead of kailh hotswap footprint
2022-07-10 Finish connecting switches after switch footprint change
2022-07-14 Create kitspace.yaml (#13)
2022-07-18 Add a top plate project file
2022-07-22 Add some probe-rs documentation
2022-07-22 Don't send a key scan code for the Fn key
2022-07-25 Update the footprints for the top plate
2022-07-25 Add production files for the top plate
2022-07-26 Small tweaks before version 0.2
2022-07-26 Add instructions for generating files for JLCPCB
2022-07-26 Add production files for v0.2
2022-08-11 Jump to the USB mass-storage bootloader if the Escape key is held down during power-on (#17)
2022-08-17 Top plate v0.1 (#19)
    * Add a top plate project file
    * Update top plate footprints
    * Update the footprints for the top plate
    * Add production files for the top plate
2022-08-17 Add the kicad-keyboard-parts repo as a submodule
2022-08-17 Adjust the silkscreen to be on the front side, mark it v0.2
2022-10-10 Temp work switching to usbd_human_interface_device
2022-10-12 update rp2040-hal dependency
2022-10-12 send reports back in interrupt handler
2022-10-12 remove unused code
2022-10-12 remove all timer-related code
2022-10-12 Add github actions files
2022-10-12 Add a default working directory
2022-10-12 Try a different way of changing the directory
2022-10-12 add a simple debouncer
2022-10-12 some debounce code cleanups
2022-10-12 cleanup unwanted diffs
2022-10-12 make variable names more self-documenting
2022-10-12 simplify debounce countdown logic
2022-10-12 document the struct fields
2022-10-12 cleanup main.rs a bit
2022-10-12 refactor scanning and debouncing logic into a KeyScan struct
2022-10-12 bust out KeyScan into its own file for cleanliness
2022-10-12 get rid of the Option wrapper in KEYBOARD_REPORT
2022-10-12 take as much code out of critical sections as possible
2022-10-13 i guess you have to pull raw output
2022-10-18 fix clippy
2022-10-18 don't debounce modifier keys
2022-10-20 latency and accuracy improvements (#25)
    * update rp2040-hal dependency
    * interrupts work
    * send reports back in interrupt handler
    * remove unused code
    * remove all timer-related code
    * update defmt-rtt
2022-11-10 Update the footprint library table
2022-11-10 Update stabilizer footprints
2022-11-10 Update switch footprints
2022-11-11 Update remaining footprints and fill zones
2022-11-12 Add kicad-parts as a submodule
2022-11-12 Manually change a few footprints to SMD/through-hole
2022-11-13 Fix the boot keyboard HID descriptor
2022-11-13 Support remote wakeup
2022-11-13 Implement remote wakeup
2022-11-28 Default to elf2uf2 for running
2022-12-01 Update kicad-parts lib
2022-12-03 Remove M2 mounting holes
2022-12-03 Update kicad-parts
2022-12-04 Re-route some of the lower matrix lines to make space for a threaded insert
2022-12-04 Add threaded PCB insertsj, clean up switch matrix wiring
2022-12-04 Slight track cleanups
2022-12-17 Add pass-through holes for the M2 hex spacers
2022-12-20 allow for Fn key to be anywhere on keyboard
2022-12-20 add parens keycodes
2022-12-28 Add edge cutouts
2022-12-30 Slightly consolidate passive values
2022-12-30 Add M2 spacer pass-through mounting holes to the schematic
2022-12-30 Update kicad-parts library
2022-12-30 Add a USB net class, make the USB lines thicc to get impedance close to 90 ohms
2022-12-30 Length match the USB lines
2022-12-30 Clean up some tracks
2022-12-30 Fix a lot of silkscreen issues
2022-12-31 More silkscreen fixups
2022-12-31 Update keyboard parts library
2023-01-01 Add various test points
2023-01-02 Move resistors to 1608 metric size
2023-01-02 Change the crystal capacitor footprints to 1608 metric size
2023-01-02 Track visual aesthetics adjustments
2023-01-04 Finish adding LCSC part numbers
2023-01-05 Add TRRS connector parts
2023-01-05 Add a test point for providing a 5V debug power supply (if you want to avoid USB bus power)
2023-01-05 Update fill zones
2023-01-06 Simplify track routes for the keyboard matrix
2023-01-06 Update keyboard parts lib
2023-01-06 Clean up silkscreens on the front
2023-01-06 Make the silkscreens prettier
2023-01-06 Make the resistors around the USB boot button a little easier to hand solder
2023-01-06 Rearrange some silkscreen labels
2023-01-08 Use a much smaller flash chip
2023-01-08 Remove QSPI test points
2023-01-08 Small component placement adjustments
2023-01-27 Label the user LED
2023-01-28 Move the F1-F4 keys over to line up with number keys
2023-01-28 Center the upper left notch
2023-01-28 Restructure production files
2023-01-28 Clean up the top-plate
2023-01-28 Re-align top plate to the same grid as the PCB
2023-01-29 Add the remaining M2 holes for the top plate
2023-01-29 Add the bottom plate
2023-01-31 Update kitspace.yaml (#44)
2023-01-31 Fix top-plate gerber path in kitspace.yaml
2023-01-31 Update bottom plate silkscreens
2023-01-31 Fix top-plate gerber path in kitspace.yaml (#46)
2023-02-06 Add hatching on the copper pours
2023-02-07 Update copper pour patterns library
2023-02-07 Fix the solid copper pour under the USB lines
2023-02-08 Update silkscreens on the plates
2023-02-08 Small track and silkscreen fixups
2023-02-08 Add some patterns to the top and bottom plate copper pours
2023-02-10 Initial pattern generator commit
2023-02-10 Cleanup unused code and format
2023-02-10 Add a triangle-gradient copper pour pattern to the bottom plate
2023-02-10 Pattern generator (#48)
    * Initial pattern generator commit
    * Cleanup unused code and format
    * Add a triangle-gradient copper pour pattern to the bottom plate
    * Fix a gap in the copper pour
2023-02-10 One last zone fill before ordering
2023-02-10 Make the pattern square size 2.5mm instead of 5mm
2023-02-10 Hide silkscreens on the top plate
2023-02-10 Add pattern-generator .gitignore
2023-02-10 Add pattern-generator rustfmt file
2023-02-11 Simplifications to pattern-generator
2023-02-18 Remove unnecessary schematics directory
2023-02-18 Update footprints on all boards
2023-04-19 allow for Fn key to be anywhere on keyboard (#50)
    * add parens keycodes
    * allow for Fn key to be anywhere on keyboard
2023-04-23 Change top plate cutouts to pcb-mounted stabilizer style
2023-05-30 Update dependencies
2023-11-06 Add support for dega-chan's keyboard
2023-11-07 Use the firmware working directory for cargo
2023-11-07 Fuck yaml
2023-11-12 Use a more maintained actions-rs github actions repo
2023-11-12 More CI fixes
2023-11-12 Remove teardrops added via an older plugin
2023-11-12 Add teardrops with the built-in kicad teardrop tool
2023-11-12 Use built-in kicad teardrops (#51)
    * Remove teardrops added via an older plugin
    * Add teardrops with the built-in kicad teardrop tool
2023-12-12 Only poll the USBD_HID object once per interrupt
2023-12-12 Update dependencies, remove unused import
2024-06-21 Use const generics for arrays holding the row and column pins
2024-06-21 Simplify the keymap definition (#56)
    * Use const generics for arrays holding the row and column pins
    * Simplify the keymap definition
2024-06-21 Fix the 'report_is_empty()' function
2024-06-22 Fix the 'report_is_empty()' function (#57)
2024-06-23 Update dependencies to the latest versions
2024-06-23 Update dependencies to the latest versions (#58)
2024-06-23 Add details on the v0.3 update in the README
2024-06-30 Use a count-down timer instead of a delay for hopefully more accurate key-scan timing
2024-06-30 Use a count-down timer instead of a delay for hopefully more accurate key-scan timing (#60)
2024-06-30 Define our own KeyboardReport struct instead of using usbd-hid's
2024-06-30 Don't send duplicate reports
2024-06-30 Revert dependency change
2024-06-30 Don't send duplicate reports in the interrupt handler
2024-06-30 Basic version of the HID class works
2024-06-30 Tweak the doc comments a bit
2024-07-03 Add some comments
2024-07-05 Reduce the matrix scan time from roughly 280µs to 14µs
2024-07-07 Add usbd-serial to log some timing info
2024-07-12 Don't send duplicate reports (#61)
    * Don't send duplicate reports
    * Revert dependency change
2024-07-12 NIH HID (#63)
    * Start adding our own HID class implementation
    * Basic version of the HID class works
    * Tweak the doc comments a bit
    * Add some comments
    * Remove the usbd-hid crate
    * Reduce the matrix scan time from roughly 280µs to 14µs
2024-07-12 Implement the GET_REPORT request
2024-07-12 Parse LED states, add temporary usbd-serial for logging
2024-07-12 Report key rollover when it happens
2024-07-21 Update part libraries
2024-07-21 Add an ESD protection diode to the USB lines
2024-07-21 Add ESD protection on the PCB
2024-07-21 ESD Protection (#66)
    * Add an ESD protection diode to the USB lines
    * Add ESD protection on the PCB
2024-07-25 Indicate the correct LED color
2025-03-02 Update deps
2025-03-02 Try to wake up the host if a key is pressed and we're in a suspended state
2025-03-05 Allow the static_mut_refs lint for now
2025-03-06 Re-add USB wakeup functionality (#67)
    * Try to wake up the host if a key is pressed and we're in a suspended state
    * Update rp2040-hal dep
    * Allow the static_mut_refs lint for now
2025-07-03 Add Ikumi's keymap
2025-07-03 Update the README with links to the case
2025-07-03 Add case STEP files (#68)
    * Add case STEP files
    * Update the README with links to the case
2025-12-17 Delay a bit more in the key matrix scanning logic
